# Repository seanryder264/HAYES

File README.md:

# HAYES

:(

## Group Member Roles

| | Harry | Aadin | Yuki | Ethan | Sean |
| --- | --- | --- | --- | --- | --- |
| **Week 1** | project ideas, hardware design | project ideas, setting up PYNQ board, building the starter projects, got vivado stuff set up | project ideas, variable input ideas, hardware design | project ideas, visualisation, python | Admin/Planning, Setting up simulation, project ideas, block diagram of logic |
| **Week 2** | | | | | |
| **Week 3** | | | | | |
| **Week 4** | | | | | |

## Project Planning

### Week 1 (19 - 25 May)

**Goals:** Project Decided, Planned Out, Tools set up

| Mon | Tue | Wed | Thu | Fri | Sat | Sun |
| --- | --- | --- | --- | --- | --- | --- |
| 9:00 Group Registration, 12:00 Option Allocation | 10:00 Academic Writing | 13:00 Second Year Meeting | 10:00 Ed Stott Meeting | | | |

**Proposals** - https://imperiallondon-my.sharepoint.com/:w:/r/personal/hh1823_ic_ac_uk/Documents/Ideas%20for%20Consultation.docx?d=w64da16023ef14e0098bc3b67b661a416&csf=1&web=1&e=dfb4Sq

Inspiration for Complex Function Colouring Proposal - https://www.algorithm-archive.org/contents/domain_coloring/domain_coloring.html

### Week 2 (26 - 1 Jun)

**Goals:** Working Prototype

| Mon | Tue | Wed | Thu | Fri | Sat | Sun |
| --- | --- | --- | --- | --- | --- | --- |
| | 14:00 Advice for EE2 | | | | | |

### Week 3 (2 - 8 Jun)

**Goals:** Itterate on prototype, Hardware working

| Mon | Tue | Wed | Thu | Fri | Sat | Sun |
| --- | --- | --- | --- | --- | --- | --- |
| Interim Presentation  | | | | | | |

### Week 4 (9 - 15 Jun)

**Goals:** Finishing touches

| Mon | Tue | Wed | Thu | Fri | Sat | Sun | Mon |
| --- | --- | --- | --- | --- | --- | --- | --- |
|  | | | | | | | **Demo Day** |

## Interim Presentation

https://docs.google.com/presentation/d/1BTT8j2C3yh5_B_K2_p1NdAU0HLvElthAQJqZgBe2U2k/edit?slide=id.g35f5acde5a9_1_14

## Report

https://www.overleaf.com/3583842195knwrcvvsffbx#b1fd1f

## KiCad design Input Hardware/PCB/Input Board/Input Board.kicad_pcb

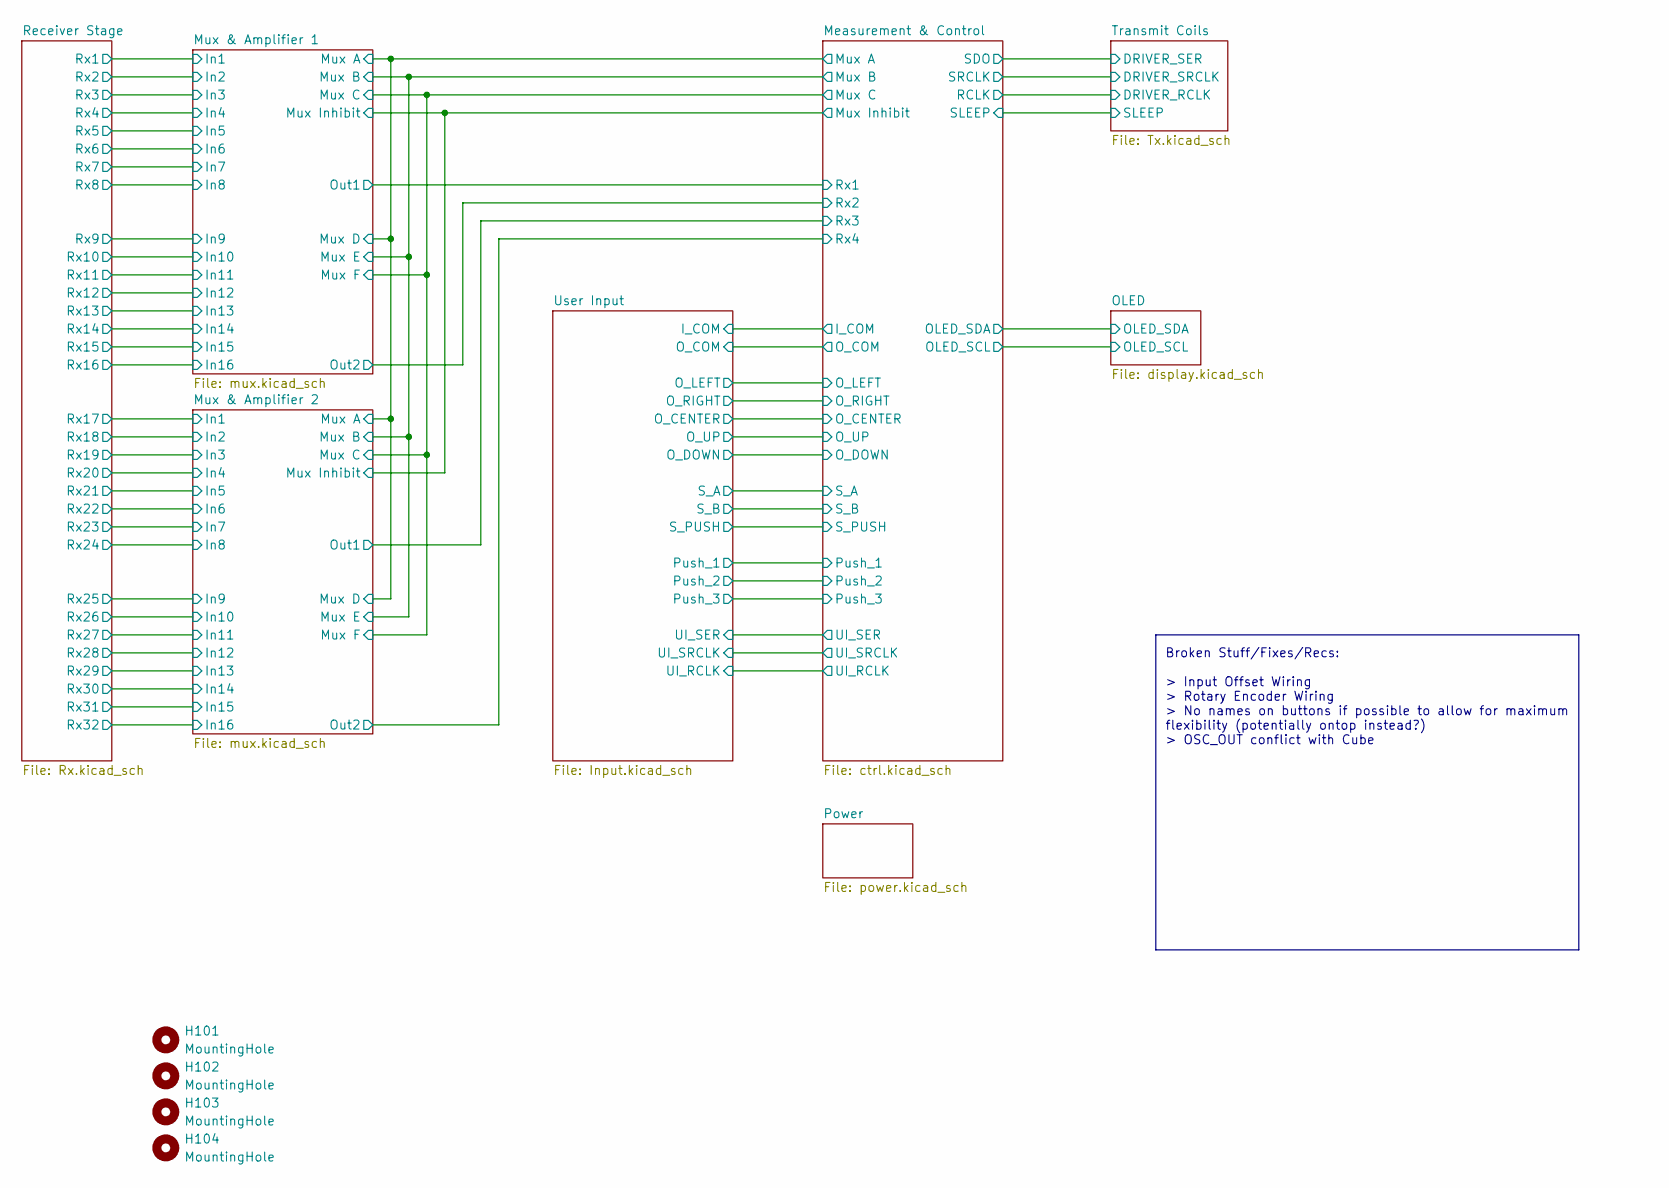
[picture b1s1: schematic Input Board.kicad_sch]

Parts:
H101, H102, H103, H104: MountingHole; MountingHole_3.2mm_M3

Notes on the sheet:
Broken Stuff/Fixes/Recs: > Input Offset Wiring > Rotary Encoder Wiring > No names on buttons if possible to allow for maximum flexibility (potentially ontop instead?) > OSC_OUT conflict with Cube

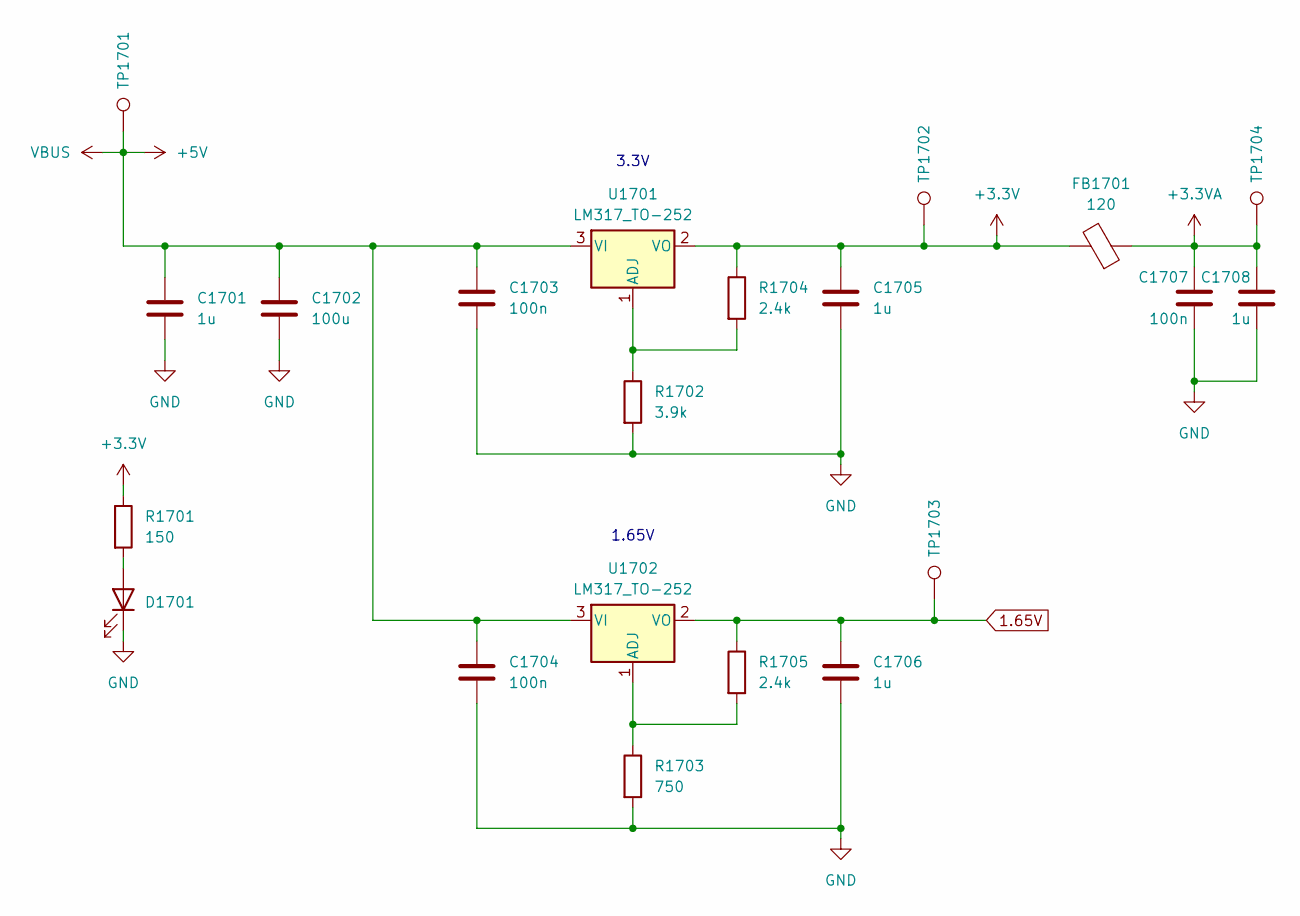
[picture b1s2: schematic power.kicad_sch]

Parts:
C1701, C1705, C1706: 1u; C_0603_1608Metric
C1702: 100u; C_Elec_4x5.8
C1703, C1704: 100n; C_0603_1608Metric
C1707: 100n; C_0603_1608Metric; Manufacturer Part Number CL05B104KB54PNC; JLC Part Type Basic
C1708: 1u; C_0603_1608Metric; Manufacturer Part Number CL21B105KBFNNNE; JLC Part Type Basic
D1701: LED_0603_1608Metric
FB1701: 120; L_1206_3216Metric
R1701: 150; R_0603_1608Metric
R1702: 3.9k; R_0603_1608Metric
R1703: 750; R_0603_1608Metric
R1704, R1705: 2.4k; R_0603_1608Metric
TP1701, TP1702, TP1703, TP1704: TestPoint; TestPoint_Pad_1.5x1.5mm
U1701, U1702: LM317_TO-252; SOT-89-3

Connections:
1.65V: C1706.1, R1705.1, TP1703.1, U1702.2 (VO); also elsewhere on the board
+3.3V: C1705.1, FB1701.2, R1701.1, R1704.1, TP1702.1, U1701.2 (VO); also elsewhere on the board
+3.3VA: C1707.1, C1708.1, FB1701.1, TP1704.1; also elsewhere on the board
+5V: C1701.1, C1702.1, C1703.1, C1704.1, TP1701.1, U1701.3 (VI), U1702.3 (VI); also elsewhere on the board
unnamed: D1701.2 (A), R1701.2
unnamed: R1702.1, R1704.2, U1701.1 (ADJ)
unnamed: R1703.1, R1705.2, U1702.1 (ADJ)

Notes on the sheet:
1.65V
3.3V

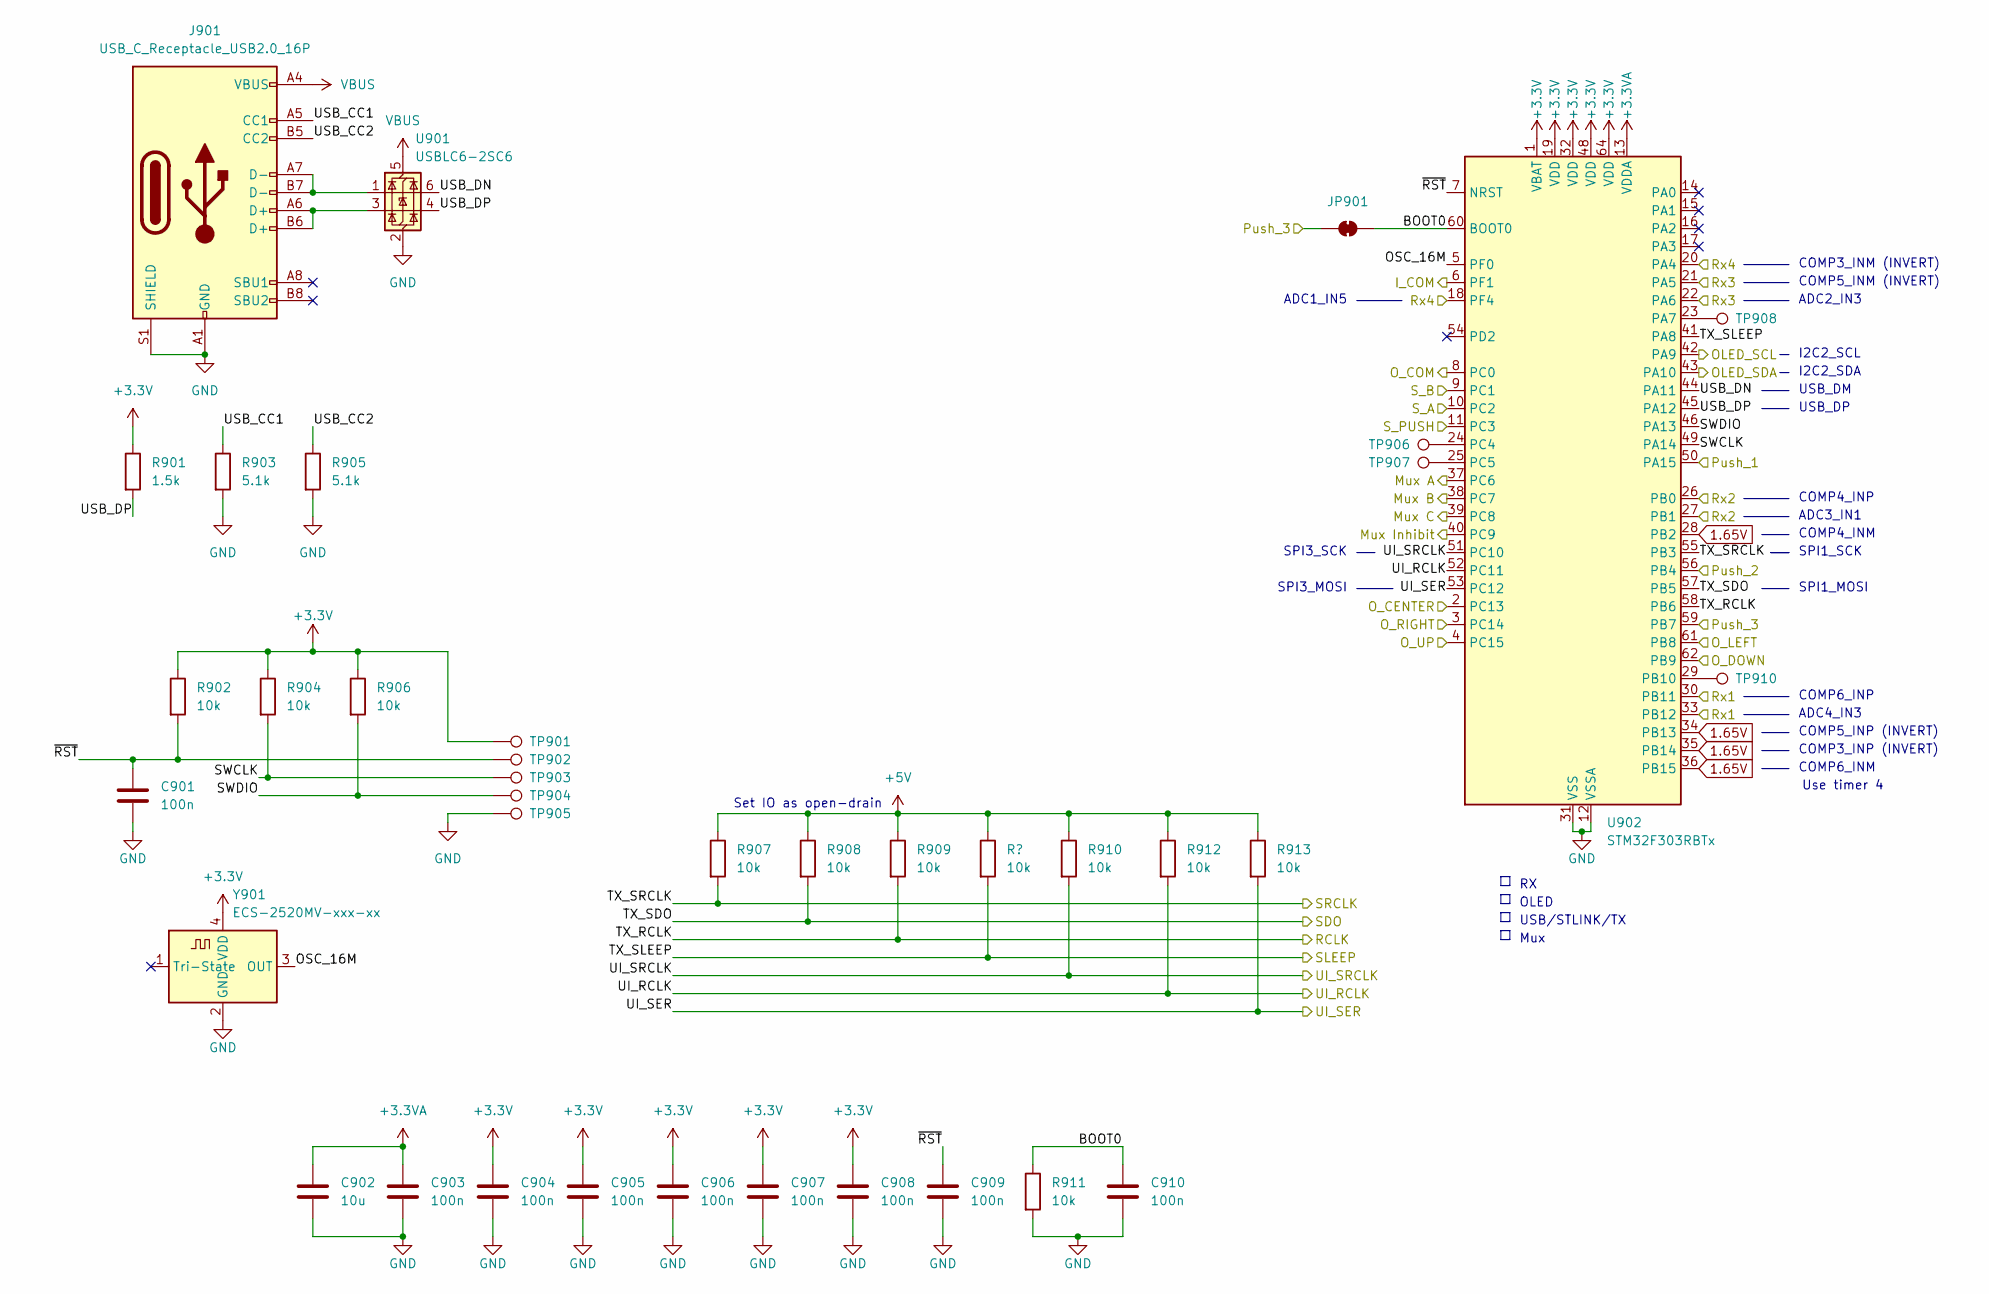
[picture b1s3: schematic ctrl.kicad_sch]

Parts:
C901, C903, C904, C905, C906, C907, C908, C909, C910: 100n; C_0603_1608Metric
C902: 10u; C_0603_1608Metric
J901: USB_C_Receptacle_USB2.0_16P; USB_C_Receptacle_GCT_USB4110
JP901: SolderJumper_2_Bridged; SolderJumper-2_P1.3mm_Bridged_RoundedPad1.0x1.5mm
R901: 1.5k; R_0603_1608Metric
R902, R904, R906, R907, R908, R909, R910, R911, R912, R913: 10k; R_0603_1608Metric
R903, R905: 5.1k; C_0603_1608Metric
TP901, TP902, TP903, TP904, TP905, TP906, TP907, TP908, TP910: TestPoint; TestPoint_Pad_1.5x1.5mm
U901: USBLC6-2SC6; SOT-23-6
U902: STM32F303RBTx; LQFP-64_10x10mm_P0.5mm
Y901: ECS-2520MV-xxx-xx; Oscillator_SMD_ECS_2520MV-xxx-xx-4Pin_2.5x2.0mm

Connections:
1.65V: U902.28 (PB2), U902.34 (PB13), U902.35 (PB14), U902.36 (PB15); also elsewhere on the board
+3.3V: C904.1, C905.1, C906.1, C907.1, C908.1, R901.1, R902.1, R904.1, R906.1, TP901.1, U902.1 (VBAT), U902.19 (VDD), U902.32 (VDD), U902.48 (VDD), U902.64 (VDD), Y901.4 (VDD); also elsewhere on the board
+3.3VA: C902.1, C903.1, U902.13 (VDDA); also elsewhere on the board
+5V: J901.A4 (VBUS), J901.A9 (VBUS), J901.B4 (VBUS), J901.B9 (VBUS), R907.1, R908.1, R909.1, R910.1, R912.1, R913.1, U901.5 (VBUS); also elsewhere on the board
/Measurement & Control/BOOT0: C910.1, JP901.2 (B), R911.1, U902.60 (BOOT0)
/Measurement & Control/I_COM: U902.6 (PF1); also elsewhere on the board
/Measurement & Control/Mux A: U902.37 (PC6); also elsewhere on the board
/Measurement & Control/Mux B: U902.38 (PC7); also elsewhere on the board
/Measurement & Control/Mux C: U902.39 (PC8); also elsewhere on the board
/Measurement & Control/Mux Inhibit: U902.40 (PC9); also elsewhere on the board
/Measurement & Control/OLED_SCL: U902.42 (PA9); also elsewhere on the board
/Measurement & Control/OLED_SDA: U902.43 (PA10); also elsewhere on the board
/Measurement & Control/OSC_16M: U902.5 (PF0), Y901.3 (OUT)
/Measurement & Control/O_CENTER: U902.2 (PC13); also elsewhere on the board
/Measurement & Control/O_COM: U902.8 (PC0); also elsewhere on the board
/Measurement & Control/O_DOWN: U902.62 (PB9); also elsewhere on the board
/Measurement & Control/O_LEFT: U902.61 (PB8); also elsewhere on the board
/Measurement & Control/O_RIGHT: U902.3 (PC14); also elsewhere on the board
/Measurement & Control/O_UP: U902.4 (PC15); also elsewhere on the board
/Measurement & Control/Push_1: U902.50 (PA15); also elsewhere on the board
/Measurement & Control/Rx1: U902.30 (PB11), U902.33 (PB12); also elsewhere on the board
/Measurement & Control/Rx2: U902.26 (PB0), U902.27 (PB1); also elsewhere on the board
/Measurement & Control/Rx3: U902.21 (PA5), U902.22 (PA6); also elsewhere on the board
/Measurement & Control/Rx4: U902.18 (PF4), U902.20 (PA4); also elsewhere on the board
/Measurement & Control/SWCLK: R904.2, TP903.1, U902.49 (PA14)
/Measurement & Control/SWDIO: R906.2, TP904.1, U902.46 (PA13)
/Measurement & Control/S_A: U902.10 (PC2); also elsewhere on the board
/Measurement & Control/S_B: U902.9 (PC1); also elsewhere on the board
/Measurement & Control/S_PUSH: U902.11 (PC3); also elsewhere on the board
/Measurement & Control/TX_RCLK: R909.2, U902.58 (PB6); also elsewhere on the board
/Measurement & Control/TX_SDO: R908.2, U902.57 (PB5); also elsewhere on the board
/Measurement & Control/TX_SRCLK: R907.2, U902.55 (PB3); also elsewhere on the board
/Measurement & Control/USB_CC1: J901.A5 (CC1), R903.1
/Measurement & Control/USB_CC2: J901.B5 (CC2), R905.1
/Measurement & Control/USB_DN: U901.6 (I/O1), U902.44 (PA11)
/Measurement & Control/USB_DP: R901.2, U901.4 (I/O2), U902.45 (PA12)
/Measurement & Control/~RST: C901.1, C909.1, R902.2, TP902.1, U902.7 (NRST)
unnamed: J901.A6 (D+), J901.B6 (D+), U901.3 (I/O2)
unnamed: J901.A7 (D-), J901.B7 (D-), U901.1 (I/O1)
unnamed: TP908.1, U902.23 (PA7)
unnamed 280: TP910.1, U902.29 (PB10); also elsewhere on the board
unnamed: TP906.1, U902.24 (PC4)
unnamed: TP907.1, U902.25 (PC5)

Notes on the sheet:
SPI3_SCK
Set IO as open-drain
SPI1_MOSI
COMP5_INM (INVERT)
ADC4_IN3
COMP3_INP (INVERT)
ADC3_IN1
COMP5_INP (INVERT)
COMP4_INP
I2C2_SCL
SPI1_SCK
ADC2_IN3
COMP3_INM (INVERT)
USB_DP
USB/STLINK/TX
COMP6_INP
ADC1_IN5
COMP4_INM
Use timer 4
SPI3_MOSI
OLED
Mux
USB_DM
COMP6_INM
I2C2_SDA

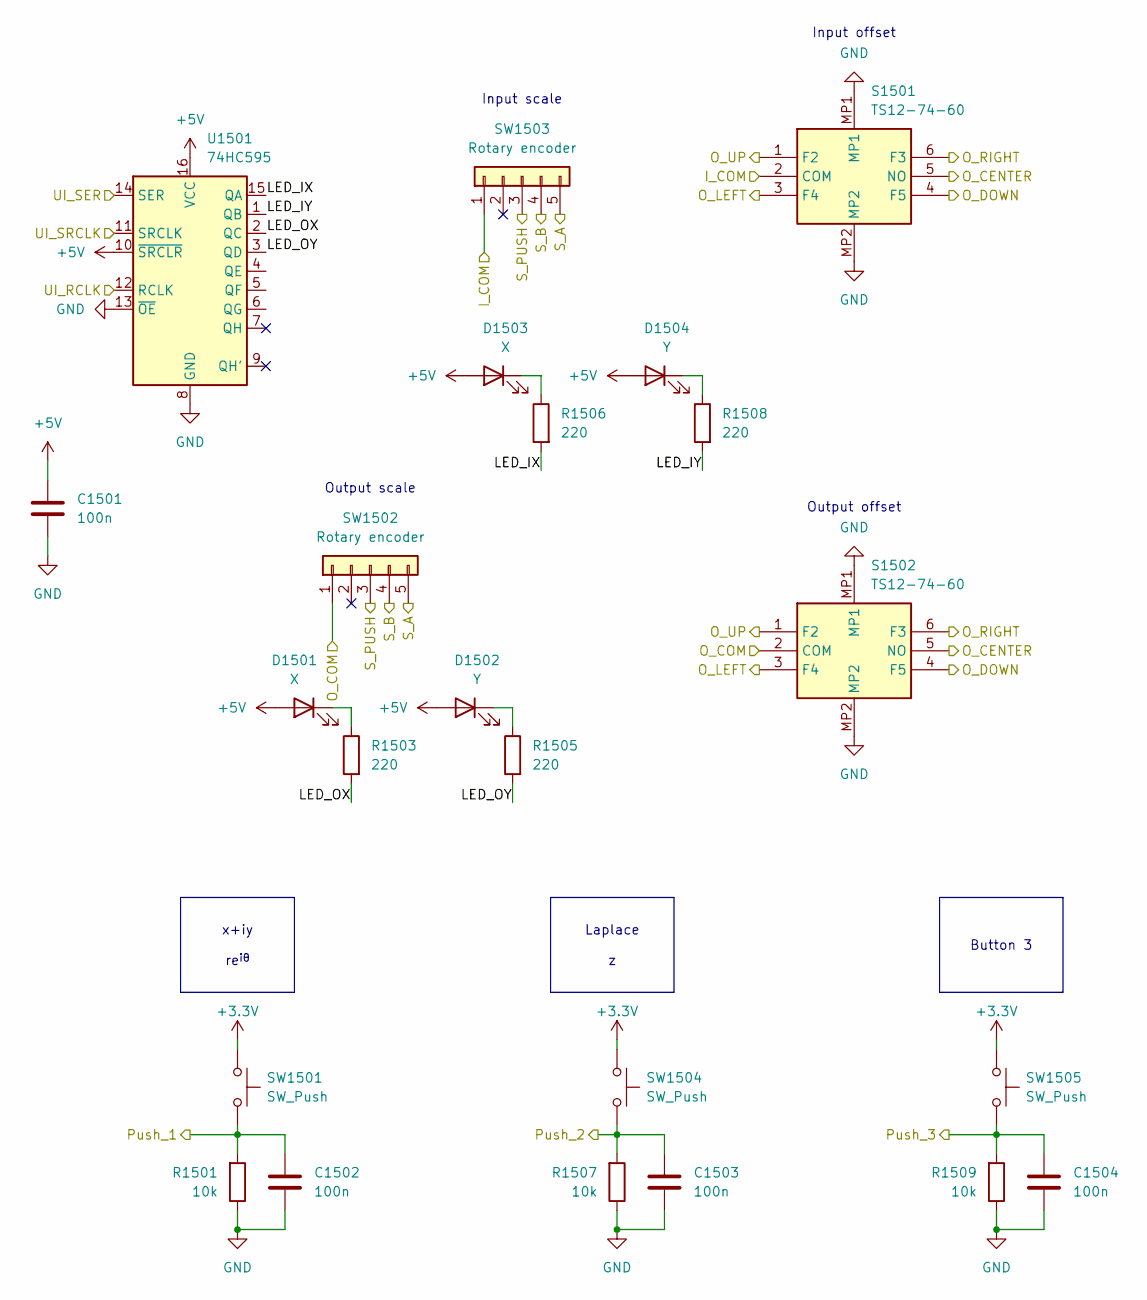
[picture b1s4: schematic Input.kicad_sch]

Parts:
C1501, C1502, C1503, C1504: 100n; C_0603_1608Metric
D1501, D1503: X; LED_0603_1608Metric
D1502, D1504: Y; LED_0603_1608Metric
R1501, R1507, R1509: 10k; R_0603_1608Metric
R1503, R1505, R1506, R1508: 220; R_0603_1608Metric
S1501, S1502: TS12-74-60; TS127460; Mouser Part Number 179-TS127460250SMTTR
SW1501, SW1504, SW1505: SW_Push; SW_SPST_B3S-1000
SW1502, SW1503: Rotary encoder; Untitled
U1501: 74HC595; DHVQFN-16-1EP_2.5x3.5mm_P0.5mm_EP1x2mm

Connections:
+3.3V: SW1501.1, SW1504.1, SW1505.1; also elsewhere on the board
+5V: C1501.1, D1501.2 (A), D1502.2 (A), D1503.2 (A), D1504.2 (A), U1501.10 (~SRCLR), U1501.16 (VCC); also elsewhere on the board
/Measurement & Control/I_COM: S1501.2 (COM), SW1503.1; also elsewhere on the board
/Measurement & Control/O_CENTER: S1501.5 (NO), S1502.5 (NO); also elsewhere on the board
/Measurement & Control/O_COM: S1502.2 (COM), SW1502.1; also elsewhere on the board
/Measurement & Control/O_DOWN: S1501.4 (F5), S1502.4 (F5); also elsewhere on the board
/Measurement & Control/O_LEFT: S1501.3 (F4), S1502.3 (F4); also elsewhere on the board
/Measurement & Control/O_RIGHT: S1501.6 (F3), S1502.6 (F3); also elsewhere on the board
/Measurement & Control/O_UP: S1501.1 (F2), S1502.1 (F2); also elsewhere on the board
/Measurement & Control/Push_1: C1502.1, R1501.2, SW1501.2; also elsewhere on the board
/Measurement & Control/S_A: SW1502.5, SW1503.5; also elsewhere on the board
/Measurement & Control/S_B: SW1502.4, SW1503.4; also elsewhere on the board
/Measurement & Control/S_PUSH: SW1502.3, SW1503.3; also elsewhere on the board

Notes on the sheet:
Input offset
Output offset
Input scale
Output scale
x+iy re^{iθ}
Button 3
Laplace z

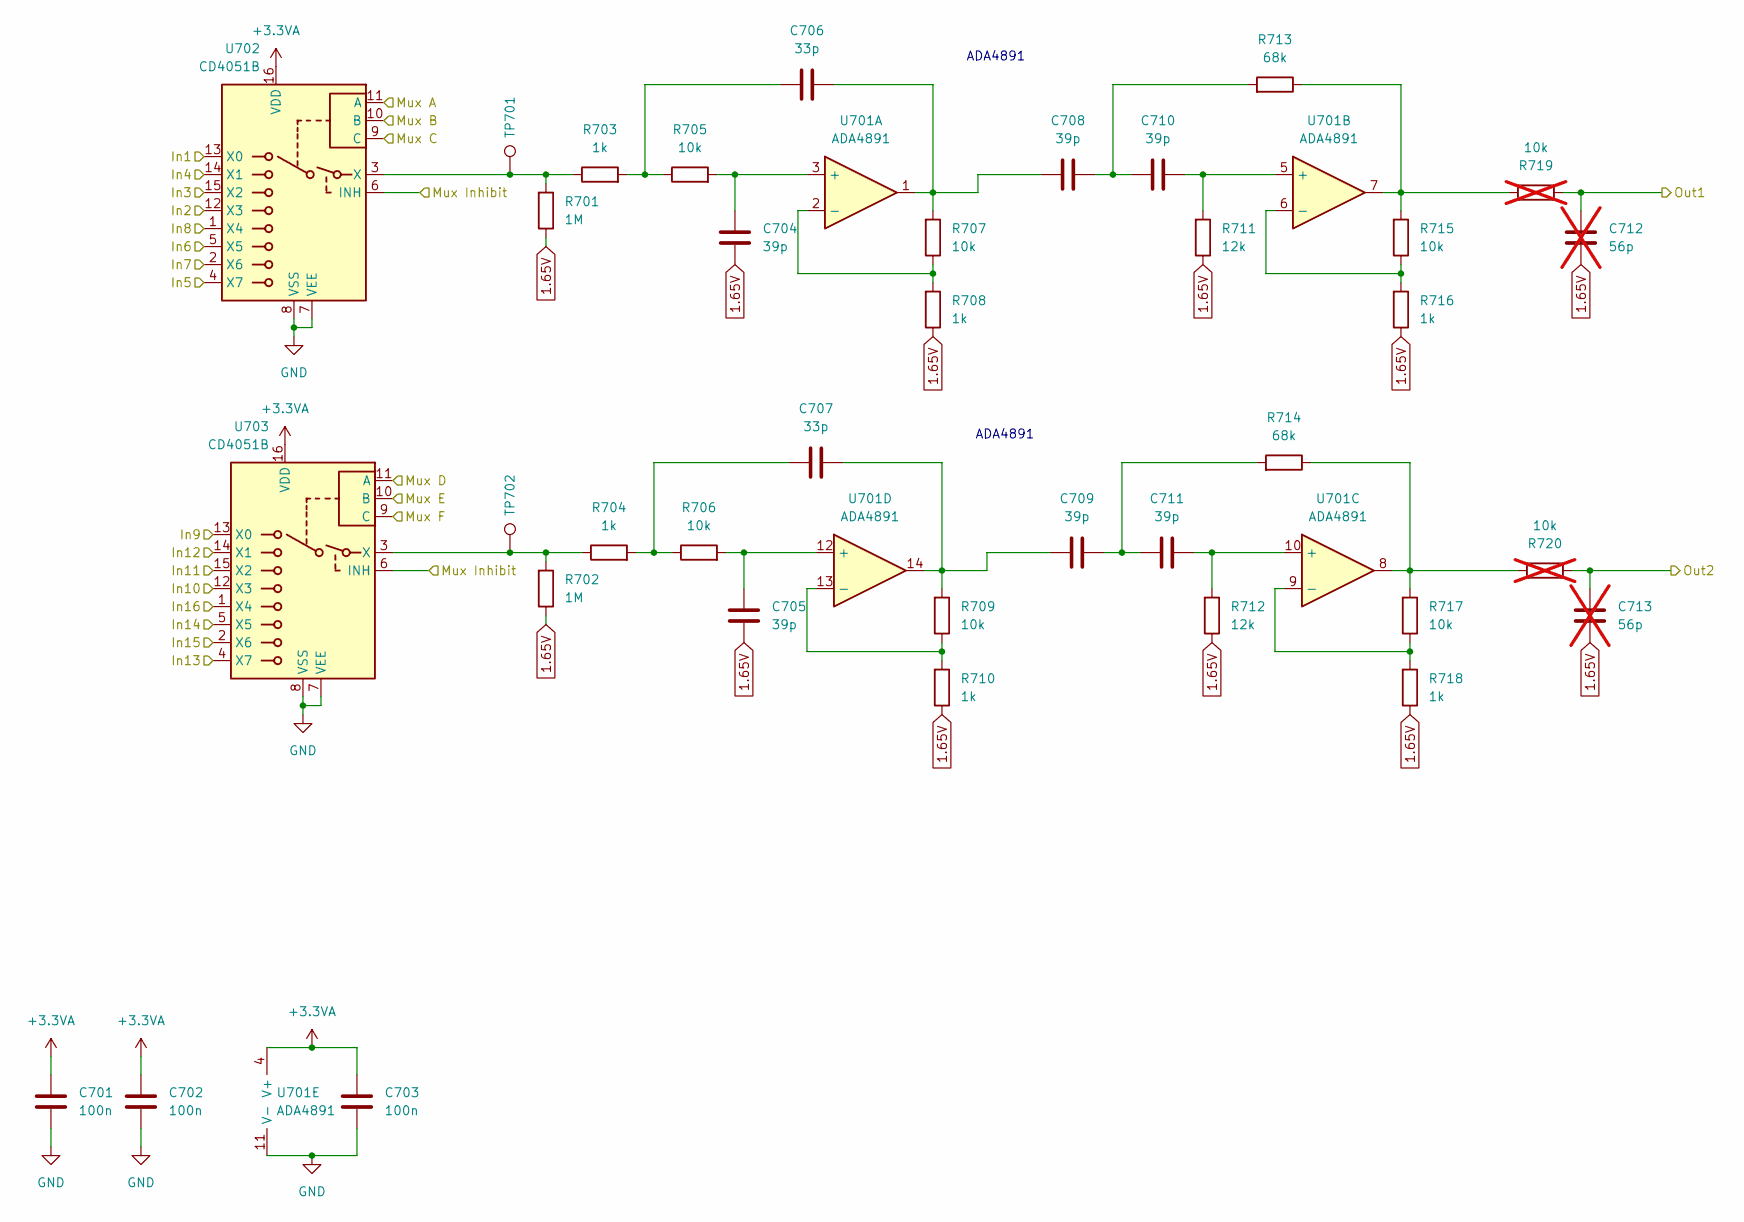
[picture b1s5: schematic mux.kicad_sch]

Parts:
C701, C702, C703: 100n; C_0603_1608Metric
C704, C705, C708, C709, C710, C711: 39p; C_0603_1608Metric
C706, C707: 33p; C_0603_1608Metric
C712, C713: 56p; C_0603_1608Metric; not fitted
R701, R702: 1M; R_0603_1608Metric
R703, R704, R708, R710, R716, R718: 1k; R_0603_1608Metric
R705, R706, R707, R709, R715, R717: 10k; R_0603_1608Metric
R711, R712: 12k; R_0603_1608Metric
R713, R714: 68k; R_0603_1608Metric
R719, R720: 10k; R_0603_1608Metric; not fitted
TP701, TP702: TestPoint; TestPoint_Pad_1.5x1.5mm
U701: ADA4891; SOIC-14_3.9x8.7mm_P1.27mm
U702, U703: CD4051B; SOIC-16_3.9x9.9mm_P1.27mm

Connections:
1.65V: C704.2, C705.2, C712.1, C713.1, R701.1, R702.1, R708.1, R710.1, R711.1, R712.1, R716.1, R718.1; also elsewhere on the board
+3.3VA: C701.1, C702.1, C703.1, U701.4 (V+), U702.16 (VDD), U703.16 (VDD); also elsewhere on the board
/Measurement & Control/Mux A: U702.11 (A), U703.11 (A); also elsewhere on the board
/Measurement & Control/Mux B: U702.10 (B), U703.10 (B); also elsewhere on the board
/Measurement & Control/Mux C: U702.9 (C), U703.9 (C); also elsewhere on the board
/Measurement & Control/Mux Inhibit: U702.6 (INH), U703.6 (INH); also elsewhere on the board
/Measurement & Control/Rx1: C712.2, R719.1; also elsewhere on the board
/Measurement & Control/Rx2: C713.2, R720.1; also elsewhere on the board
/Mux & Amplifier 1/In1: U702.13 (X0); also elsewhere on the board
/Mux & Amplifier 1/In2: U702.12 (X3); also elsewhere on the board
/Mux & Amplifier 1/In3: U702.15 (X2); also elsewhere on the board
/Mux & Amplifier 1/In4: U702.14 (X1); also elsewhere on the board
/Mux & Amplifier 1/In5: U702.4 (X7); also elsewhere on the board
/Mux & Amplifier 1/In6: U702.5 (X5); also elsewhere on the board
/Mux & Amplifier 1/In7: U702.2 (X6); also elsewhere on the board
/Mux & Amplifier 1/In8: U702.1 (X4); also elsewhere on the board
/Mux & Amplifier 1/In9: U703.13 (X0); also elsewhere on the board
/Mux & Amplifier 1/In10: U703.12 (X3); also elsewhere on the board
/Mux & Amplifier 1/In11: U703.15 (X2); also elsewhere on the board
/Mux & Amplifier 1/In12: U703.14 (X1); also elsewhere on the board
/Mux & Amplifier 1/In13: U703.4 (X7); also elsewhere on the board
/Mux & Amplifier 1/In14: U703.5 (X5); also elsewhere on the board
/Mux & Amplifier 1/In15: U703.2 (X6); also elsewhere on the board
/Mux & Amplifier 1/In16: U703.1 (X4); also elsewhere on the board
unnamed: C706.1, R703.2, R705.1
unnamed: C706.2, C708.1, R707.2, U701.1
unnamed: C707.1, R704.2, R706.1
unnamed: C707.2, C709.1, R709.2, U701.14
unnamed: C708.2, C710.1, R713.2
unnamed: C709.2, C711.1, R714.2
unnamed: R713.1, R715.2, R719.2, U701.7
unnamed: R714.1, R717.2, R720.2, U701.8
unnamed: C704.1, R705.2, U701.3 (+)
unnamed: R707.1, R708.2, U701.2 (-)
unnamed: C710.2, R711.2, U701.5 (+)
unnamed: R715.1, R716.2, U701.6 (-)
unnamed: C711.2, R712.2, U701.10 (+)
unnamed: R717.1, R718.2, U701.9 (-)
unnamed: C705.1, R706.2, U701.12 (+)
unnamed: R709.1, R710.2, U701.13 (-)
unnamed: R701.2, R703.1, TP701.1, U702.3 (X)
unnamed: R702.2, R704.1, TP702.1, U703.3 (X)

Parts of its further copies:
C801, C802, C803: 100n; C_0603_1608Metric
C804, C805, C808, C809, C810, C811: 39p; C_0603_1608Metric
C806, C807: 33p; C_0603_1608Metric
C812, C813: 56p; C_0603_1608Metric; not fitted
R801, R802: 1M; R_0603_1608Metric
R803, R804, R808, R810, R816, R818: 1k; R_0603_1608Metric
R805, R806, R807, R809, R815, R817: 10k; R_0603_1608Metric
R811, R812: 12k; R_0603_1608Metric
R813, R814: 68k; R_0603_1608Metric
R819, R820: 10k; R_0603_1608Metric; not fitted
TP801, TP802: TestPoint; TestPoint_Pad_1.5x1.5mm
U801: ADA4891; SOIC-14_3.9x8.7mm_P1.27mm
U802, U803: CD4051B; SOIC-16_3.9x9.9mm_P1.27mm

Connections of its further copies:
1.65V: C804.2, C805.2, C812.1, C813.1, R801.1, R802.1, R808.1, R810.1, R811.1, R812.1, R816.1, R818.1; also elsewhere on the board
+3.3VA: C801.1, C802.1, C803.1, U801.4 (V+), U802.16 (VDD), U803.16 (VDD); also elsewhere on the board
/Measurement & Control/Mux A: U802.11 (A), U803.11 (A); also elsewhere on the board
/Measurement & Control/Mux B: U802.10 (B), U803.10 (B); also elsewhere on the board
/Measurement & Control/Mux C: U802.9 (C), U803.9 (C); also elsewhere on the board
/Measurement & Control/Mux Inhibit: U802.6 (INH), U803.6 (INH); also elsewhere on the board
/Measurement & Control/Rx3: C812.2, R819.1; also elsewhere on the board
/Measurement & Control/Rx4: C813.2, R820.1; also elsewhere on the board
/Mux & Amplifier 2/In1: U802.13 (X0); also elsewhere on the board
/Mux & Amplifier 2/In2: U802.12 (X3); also elsewhere on the board
/Mux & Amplifier 2/In3: U802.15 (X2); also elsewhere on the board
/Mux & Amplifier 2/In4: U802.14 (X1); also elsewhere on the board
/Mux & Amplifier 2/In5: U802.4 (X7); also elsewhere on the board
/Mux & Amplifier 2/In6: U802.5 (X5); also elsewhere on the board
/Mux & Amplifier 2/In7: U802.2 (X6); also elsewhere on the board
/Mux & Amplifier 2/In8: U802.1 (X4); also elsewhere on the board
/Mux & Amplifier 2/In9: U803.13 (X0); also elsewhere on the board
/Mux & Amplifier 2/In10: U803.12 (X3); also elsewhere on the board
/Mux & Amplifier 2/In11: U803.15 (X2); also elsewhere on the board
/Mux & Amplifier 2/In12: U803.14 (X1); also elsewhere on the board
/Mux & Amplifier 2/In13: U803.4 (X7); also elsewhere on the board
/Mux & Amplifier 2/In14: U803.5 (X5); also elsewhere on the board
/Mux & Amplifier 2/In15: U803.2 (X6); also elsewhere on the board
/Mux & Amplifier 2/In16: U803.1 (X4); also elsewhere on the board
unnamed: C806.1, R803.2, R805.1
unnamed: C806.2, C808.1, R807.2, U801.1
unnamed: C807.1, R804.2, R806.1
unnamed: C807.2, C809.1, R809.2, U801.14
unnamed: C808.2, C810.1, R813.2
unnamed: C809.2, C811.1, R814.2
unnamed: R813.1, R815.2, R819.2, U801.7
unnamed: R814.1, R817.2, R820.2, U801.8
unnamed: C804.1, R805.2, U801.3 (+)
unnamed: R807.1, R808.2, U801.2 (-)
unnamed: C810.2, R811.2, U801.5 (+)
unnamed: R815.1, R816.2, U801.6 (-)
unnamed: C811.2, R812.2, U801.10 (+)
unnamed: R817.1, R818.2, U801.9 (-)
unnamed: C805.1, R806.2, U801.12 (+)
unnamed: R809.1, R810.2, U801.13 (-)
unnamed: R801.2, R803.1, TP801.1, U802.3 (X)
unnamed: R802.2, R804.1, TP802.1, U803.3 (X)

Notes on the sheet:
ADA4891

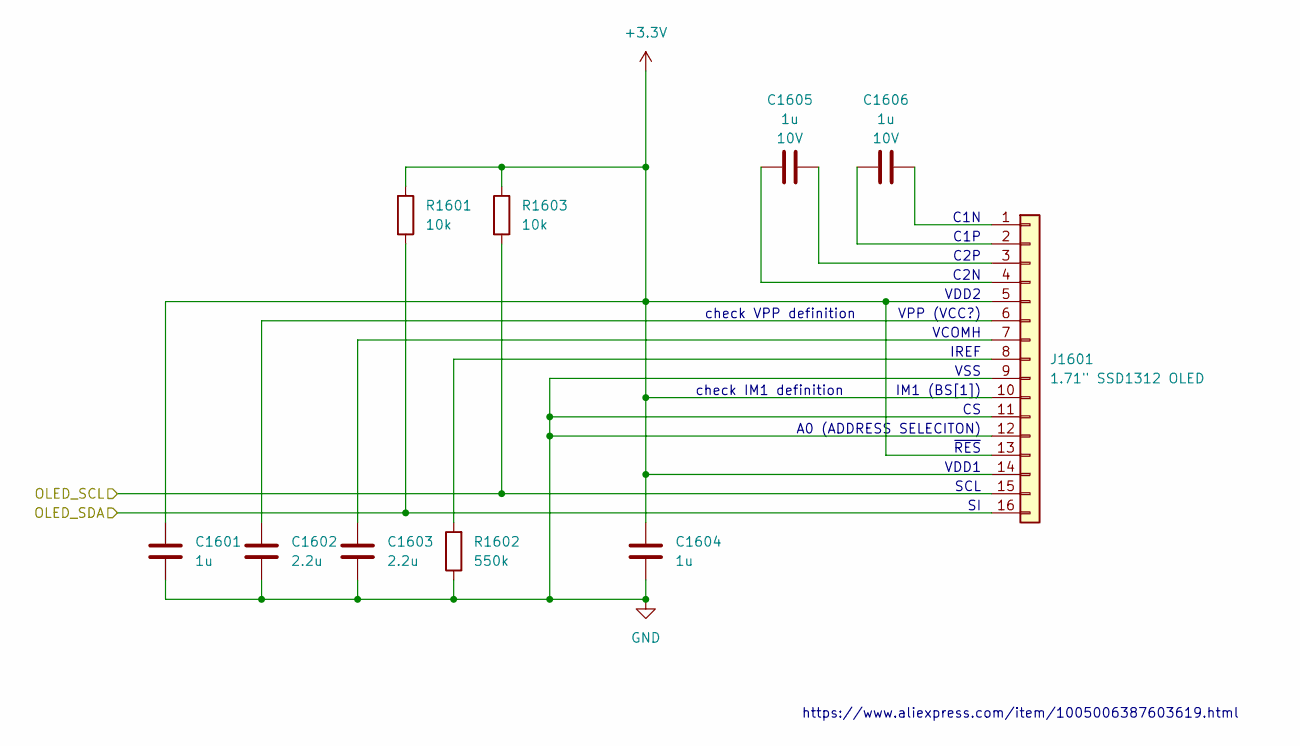
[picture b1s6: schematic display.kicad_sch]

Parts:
C1601, C1604: 1u; C_0603_1608Metric
C1602, C1603: 2.2u; C_0603_1608Metric
C1605, C1606: 1u; C_0603_1608Metric; Rating 10V
J1601: 1.71" SSD1312 OLED; 1.71 OLED SSD1312
R1601, R1603: 10k; R_0603_1608Metric
R1602: 550k; R_0603_1608Metric

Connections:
+3.3V: C1601.1, C1604.1, J1601.5, J1601.10, J1601.13, J1601.14, R1601.1, R1603.1; also elsewhere on the board
/Measurement & Control/OLED_SCL: J1601.15, R1603.2; also elsewhere on the board
/Measurement & Control/OLED_SDA: J1601.16, R1601.2; also elsewhere on the board
unnamed: C1606.2, J1601.1
unnamed: C1606.1, J1601.2
unnamed: C1605.2, J1601.3
unnamed: C1605.1, J1601.4
unnamed: C1602.1, J1601.6
unnamed: C1603.1, J1601.7
unnamed: J1601.8, R1602.2

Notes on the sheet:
~{RES}
C1P
C2P
check VPP definition
VPP (VCC?)
https://www.aliexpress.com/item/1005006387603619.html
check IM1 definition
C1N
IREF
VSS
SCL
VDD1
VDD2
A0 (ADDRESS SELECITON)
IM1 (BS[1])
VCOMH
C2N

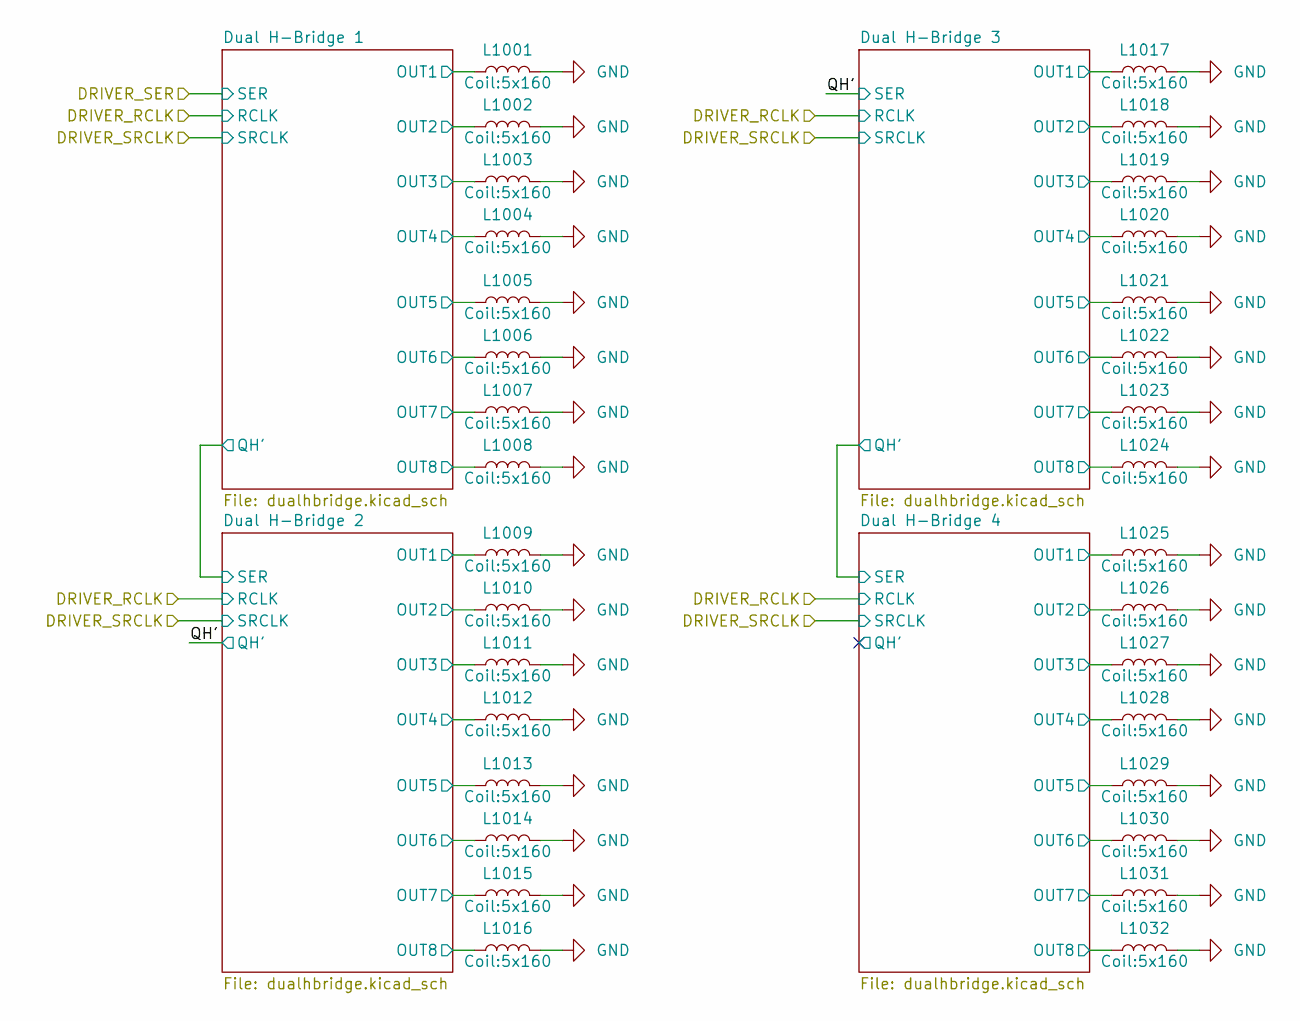
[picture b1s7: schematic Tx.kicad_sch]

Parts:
L1001, L1002, L1003, L1004, L1005, L1006, L1007, L1008, L1009, L1010, L1011, L1012, L1013, L1014, L1015, L1016, L1017, L1018, L1019, L1020, L1021, L1022, L1023, L1024, L1025, L1026, L1027, L1028, L1029, L1030, L1031, L1032: L; 5x160

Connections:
/Transmit Coils/Dual H-Bridge 1/OUT1: L1001.1; also elsewhere on the board
/Transmit Coils/Dual H-Bridge 1/OUT2: L1002.1; also elsewhere on the board
/Transmit Coils/Dual H-Bridge 1/OUT3: L1003.1; also elsewhere on the board
/Transmit Coils/Dual H-Bridge 1/OUT4: L1004.1; also elsewhere on the board
/Transmit Coils/Dual H-Bridge 1/OUT5: L1005.1; also elsewhere on the board
/Transmit Coils/Dual H-Bridge 1/OUT6: L1006.1; also elsewhere on the board
/Transmit Coils/Dual H-Bridge 1/OUT7: L1007.1; also elsewhere on the board
/Transmit Coils/Dual H-Bridge 1/OUT8: L1008.1; also elsewhere on the board
/Transmit Coils/Dual H-Bridge 2/OUT1: L1009.1; also elsewhere on the board
/Transmit Coils/Dual H-Bridge 2/OUT2: L1010.1; also elsewhere on the board
/Transmit Coils/Dual H-Bridge 2/OUT3: L1011.1; also elsewhere on the board
/Transmit Coils/Dual H-Bridge 2/OUT4: L1012.1; also elsewhere on the board
/Transmit Coils/Dual H-Bridge 2/OUT5: L1013.1; also elsewhere on the board
/Transmit Coils/Dual H-Bridge 2/OUT6: L1014.1; also elsewhere on the board
/Transmit Coils/Dual H-Bridge 2/OUT7: L1015.1; also elsewhere on the board
/Transmit Coils/Dual H-Bridge 2/OUT8: L1016.1; also elsewhere on the board
/Transmit Coils/Dual H-Bridge 3/OUT1: L1017.1; also elsewhere on the board
/Transmit Coils/Dual H-Bridge 3/OUT2: L1018.1; also elsewhere on the board
/Transmit Coils/Dual H-Bridge 3/OUT3: L1019.1; also elsewhere on the board
/Transmit Coils/Dual H-Bridge 3/OUT4: L1020.1; also elsewhere on the board
/Transmit Coils/Dual H-Bridge 3/OUT5: L1021.1; also elsewhere on the board
/Transmit Coils/Dual H-Bridge 3/OUT6: L1022.1; also elsewhere on the board
/Transmit Coils/Dual H-Bridge 3/OUT7: L1023.1; also elsewhere on the board
/Transmit Coils/Dual H-Bridge 3/OUT8: L1024.1; also elsewhere on the board
/Transmit Coils/Dual H-Bridge 4/OUT1: L1025.1; also elsewhere on the board
/Transmit Coils/Dual H-Bridge 4/OUT2: L1026.1; also elsewhere on the board
/Transmit Coils/Dual H-Bridge 4/OUT3: L1027.1; also elsewhere on the board
/Transmit Coils/Dual H-Bridge 4/OUT4: L1028.1; also elsewhere on the board
/Transmit Coils/Dual H-Bridge 4/OUT5: L1029.1; also elsewhere on the board
/Transmit Coils/Dual H-Bridge 4/OUT6: L1030.1; also elsewhere on the board
/Transmit Coils/Dual H-Bridge 4/OUT7: L1031.1; also elsewhere on the board
/Transmit Coils/Dual H-Bridge 4/OUT8: L1032.1; also elsewhere on the board
